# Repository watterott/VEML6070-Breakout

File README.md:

# VEML6070-Breakout
Breakout with Vishay VEML6070 digital UV Light Sensor.

* [Vishay VEML6070](https://www.vishay.com/docs/84277/veml6070.pdf) Light Sensor
* Detects UV light
* TWI/I2C Interface (address 0x38 and 0x39)
* 3.3V - 5V Power Supply and Logic Level
* Open-Source and released under the [Creative Commons Attribution Share-Alike License](https://creativecommons.org/licenses/by-sa/4.0/).
* **[Documentation on learn.watterott.com](https://learn.watterott.com)**

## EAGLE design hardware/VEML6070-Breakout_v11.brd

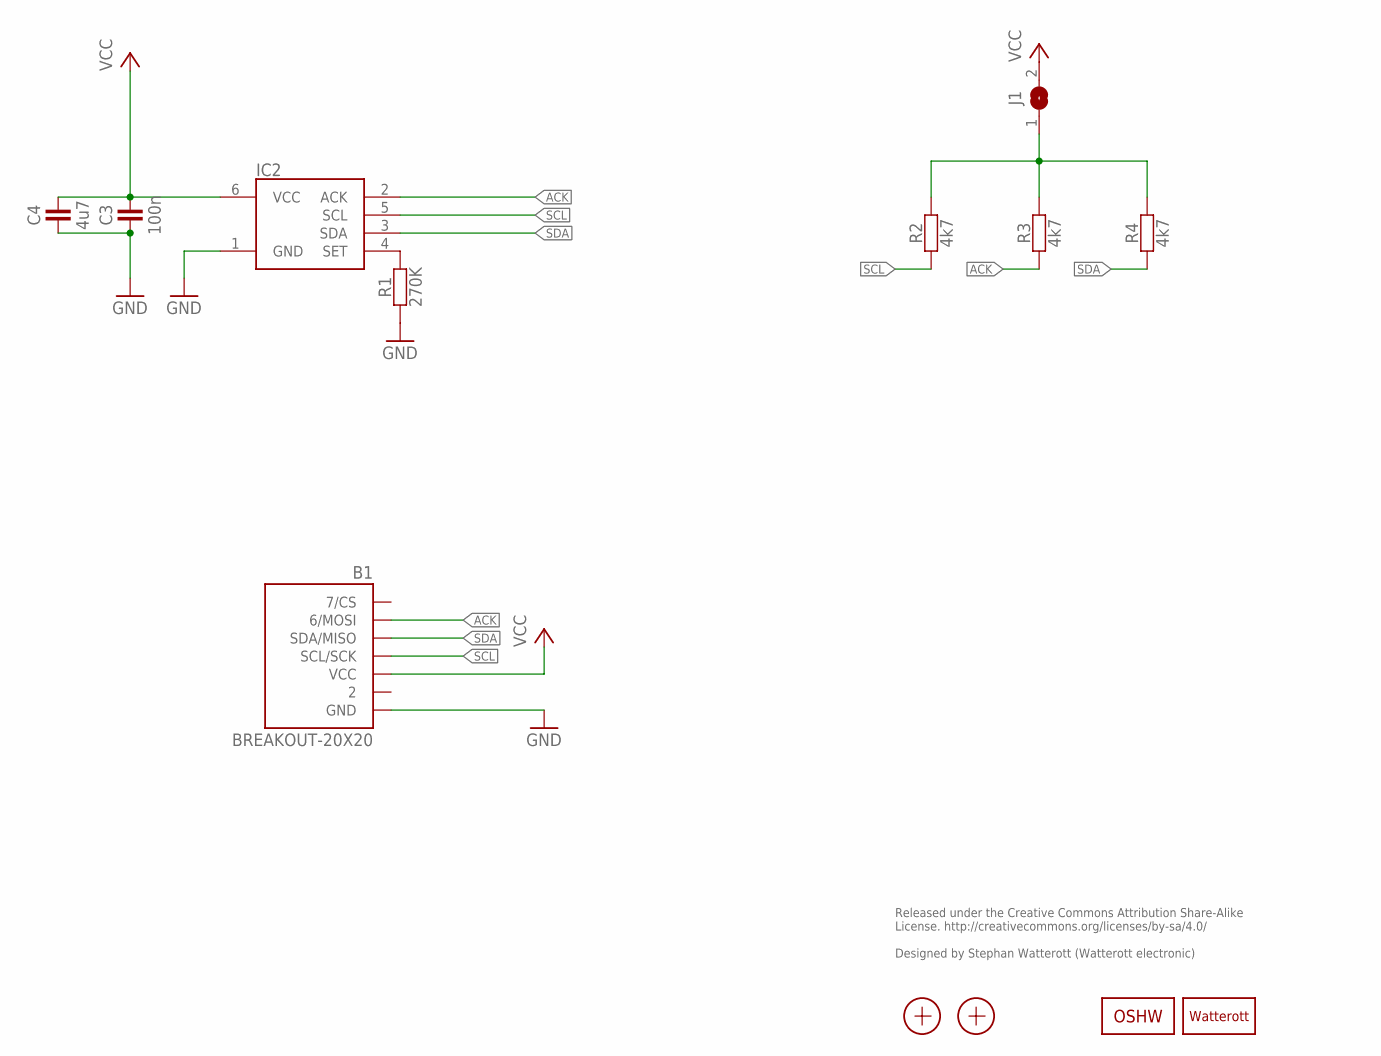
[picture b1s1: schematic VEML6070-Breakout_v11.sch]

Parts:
B1: BREAKOUT-20X20
C3: 100n; R0402
C4: 4u7; R0402
IC2: VEML6070; OPLGA
J1: JUMPER2-0603-NC; JUMPER2-0603_NC
LOGO1: LOGO-S_PLACE_M; SPARK_TPLACE_M
LOGO2: OSHW_LOGOX0070; OSHW_6X70
R1: 270K; R0402
R2, R3, R4: 4k7; R0402
X1, X2: PASSER-07; PASSER_07MM

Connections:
ACK: B1.MOSI (6/MOSI), IC2.2 (ACK), R3.1
GND: B1.GND, C3.1, C4.1, IC2.1 (GND), R1.1
unnamed: IC2.4 (SET), R1.2
unnamed: J1.1, R2.2, R3.2, R4.2
SCL: B1.SCL/SCK, IC2.5 (SCL), R2.1
SDA: B1.SDA/MISO, IC2.3 (SDA), R4.1
VCC: B1.VCC, C3.2, C4.2, IC2.6 (VCC), J1.2

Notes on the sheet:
Released under the Creative Commons Attribution Share-Alike License. http://creativecommons.org/licenses/by-sa/4.0/ Designed by Stephan Watterott (Watterott electronic)

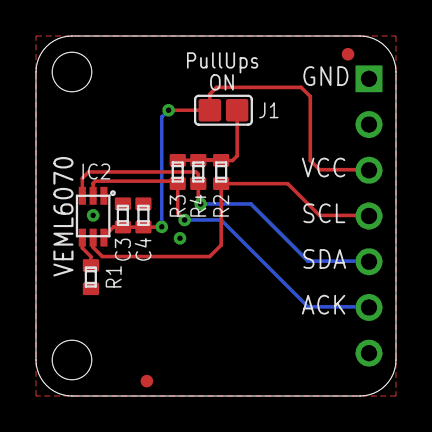
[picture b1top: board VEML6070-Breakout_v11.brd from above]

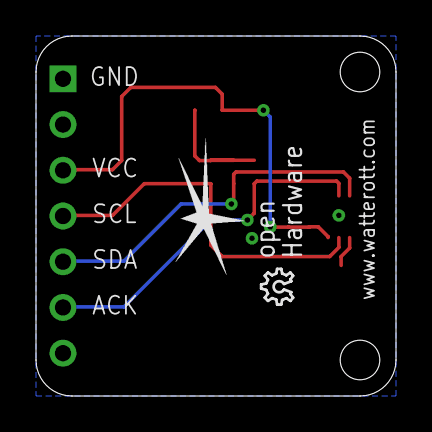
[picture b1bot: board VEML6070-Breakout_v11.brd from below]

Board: 2 copper layers, 20.0 x 20.0 mm, 13 parts (2 on the bottom side), 7 nets.

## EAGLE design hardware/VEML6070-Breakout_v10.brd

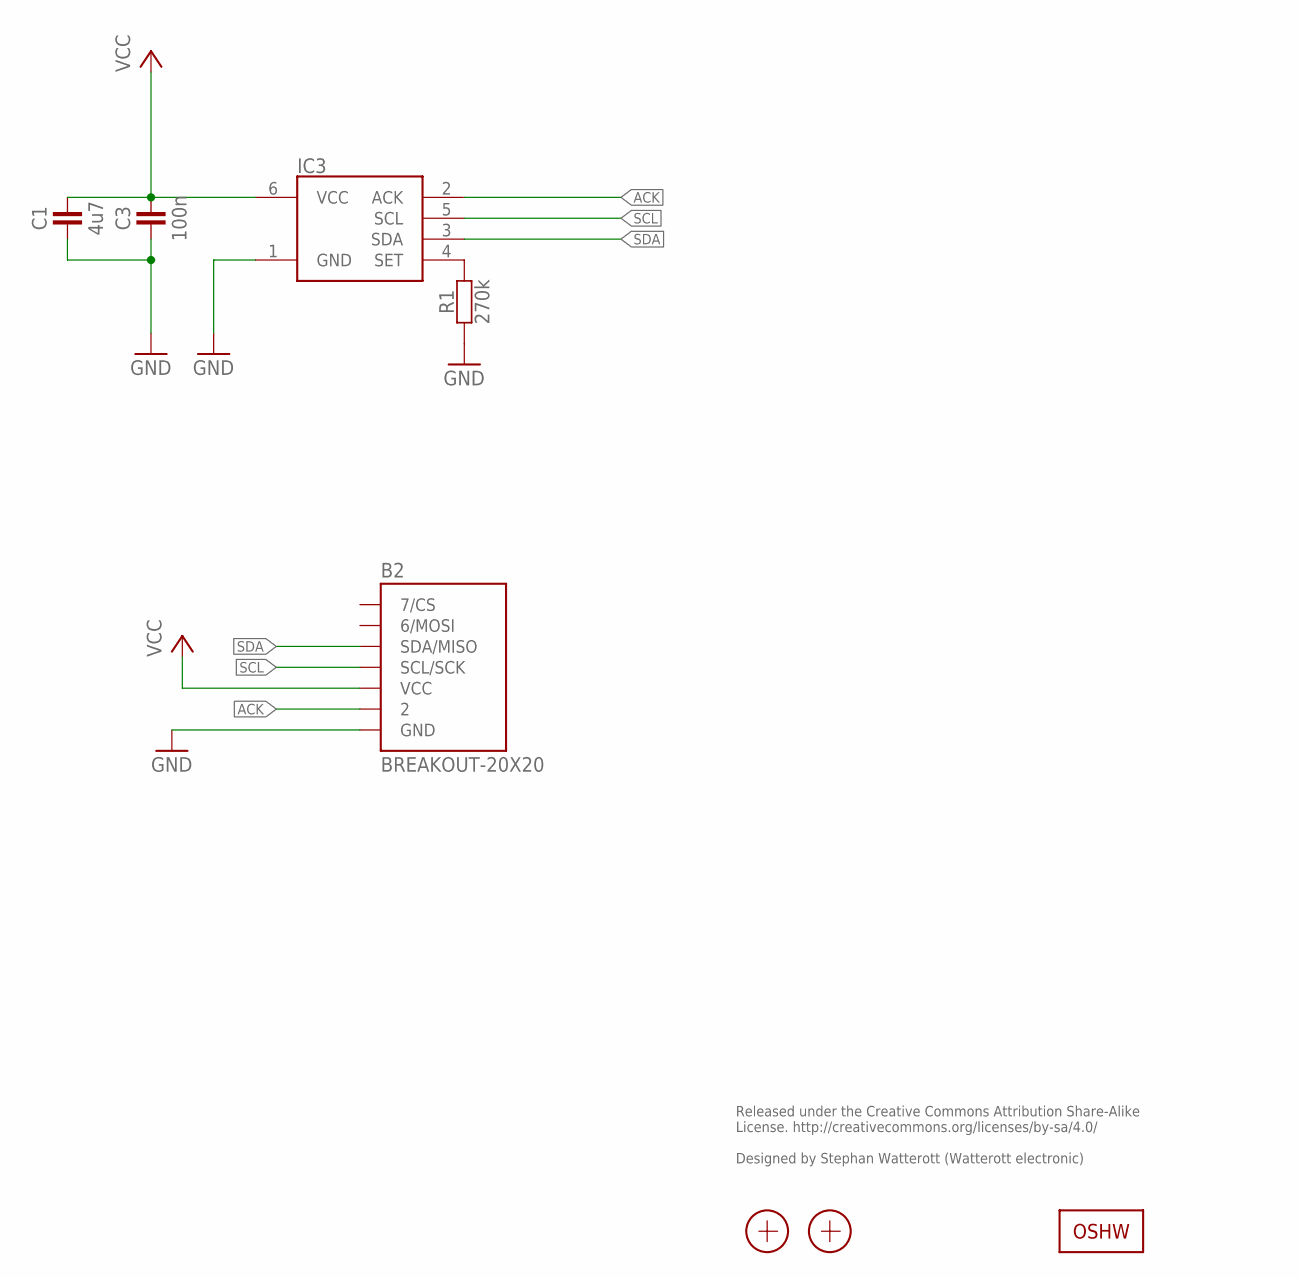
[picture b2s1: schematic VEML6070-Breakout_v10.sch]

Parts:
B2: BREAKOUT-20X20
C1: 4u7; R0402
C3: 100n; R0402
IC3: VEML6070; OPLGA
LOGO2: OSHW_LOGOX0070; OSHW_6X70
R1: 270k; R0402
X1, X2: PASSER-07; PASSER_07MM

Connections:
ACK: B2.2, IC3.2 (ACK)
GND: B2.GND, C1.1, C3.1, IC3.1 (GND), R1.1
unnamed: IC3.4 (SET), R1.2
SCL: B2.SCL/SCK, IC3.5 (SCL)
SDA: B2.SDA/MISO, IC3.3 (SDA)
VCC: B2.VCC, C1.2, C3.2, IC3.6 (VCC)

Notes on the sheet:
Released under the Creative Commons Attribution Share-Alike License. http://creativecommons.org/licenses/by-sa/4.0/ Designed by Stephan Watterott (Watterott electronic)

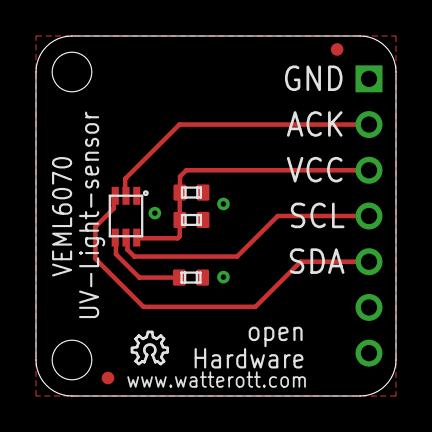
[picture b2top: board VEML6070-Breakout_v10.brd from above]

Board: 2 copper layers, 20.0 x 20.0 mm, 8 parts (0 on the bottom side), 6 nets.

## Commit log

2020-05-16 added license info
